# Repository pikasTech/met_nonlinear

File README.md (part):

# 电化学非线性矫正

# 2024年6月10日

1. 做非线性的数据收集，其中包括对震级的精确标定
2. 研究可以收集数据的范围
3. 在拓展可以收集的数据的范围之前，也可以先把数据的加载和处理流程进行处理

对于1，可以使用激光的数据来做标定

# 2024年6月11日

对绘图进行了增强，支持点选数据标签

激光测量结果（前9个点）：

加入校准系数后

# 2024年6月12日

考虑如何将数据加载到模型

1. review 之前跑过的代码
2. 将之前的代码跑起来（选）
3. 研究之前代码的数据集的格式，考虑方案：1.格式转换/2.格式兼容
4. 将一个数据做导入
5. 将数据按照之前的方式做处理

找到之前的笔记：

> 2023年7月5日 李昂
>
> 完成了用于训练的原始时域数据的收集，并可以进行绘图：
>
> 
>
> 用LSTM模型对系统进行辨识：
>
> 
>
> 经过训练后，最好的结果是loss=16000左右：
>
> 查看预测结果：在这个片段中预测结果和实际结果的相位基本一致，但幅值差异还是很大
>
> 
>
> 在这个片段中预测结果和实际结果的相位和幅值差异都较大
>
> 
>
> 按照结果进行初步分析，认为至少直流偏置是得到了正常的辨识的，但模型整体处于欠拟合状态，不能很好地拟合目标结果
>
> 下一步计划：
>
> 1. **数据预处理和特征工程**：
>    - 对原始时域数据进行进一步的预处理，例如去除噪声、归一化等，以提高数据质量和模型训练效果。
>    - 考虑是否需要进行特征工程，例如提取频域特征或其他相关特征，以增加模型的输入维度和表达能力。
> 2. **模型调优**：
>    - 调整模型的超参数，例如LSTM层的神经元数量、层数，调整优化器的学习率和其他参数，以提高模型的拟合能力和性能。
>    - 尝试其他类型的模型或改进的神经网络结构，例如带有注意力机制的模型或Transformer模型，以便更好地捕捉信号的时序特征。
> 3. **增加训练数据**：
>    - 如果可能，收集更多的训练数据，以增加模型的训练样本数量，从而提高模型的泛化能力和鲁棒性。
>    - 确保收集到的数据具有一定的多样性和覆盖范围，以更好地涵盖系统的不同情况和特性。
> 4. **尝试其他损失函数**：
>    - 考虑使用与频率域相关的损失函数，以更好地兼顾高频信息，例如频谱损失函数或基于相干性的损失函数。
>    - 根据任务的特点和需求，探索其他合适的损失函数或自定义损失函数，以提高模型的训练效果和适应性。
> 5. **模型集成和集成学习**：
>    - 考虑使用模型集成的方法，例如将多个训练得到的模型进行集成或进行模型融合，以获得更好的预测性能和鲁棒性。
>    - 探索集成学习的技术，例如投票、堆叠等，以提高模型的泛化能力和抗噪性。
> 6. **模型评估和性能分析**：
>    - 对模型的训练和预测结果进行全面的评估和分析，包括对预测结果的幅值、相位等进行进一步的统计和比较。
>    - 使用其他指标来评估模型的性能，例如均方根误差（RMSE）、平均绝对误差（MAE）等，以全面了解模型的预测能力和偏差。
>
> 2023年7月6日 李昂
>
> 考虑将进行多种时间尺度的采样（1Khz采样率、100Hz采样率等）同时纳入特征的方式来补充特征中的低频信息。
>
> 
>
> 三个时间尺度的采样拼合成特征，最后得到一个（48，1）形状的特征
>
> 
>
> 但是训练失败了，loss变成了nan
>
> 改变特征形状
>
> 特征形状改为(8,4)的训练效果：
>
> 
>
> 拟合效果：
>
> 
>
> 
>
> 
>
> 可以看到在高频和低频的拟合效果在一些部分都已经很好，但是当实际值频率高且有较大的偏置时预测曲线不能很好地反映偏置。

切到23年7月8日的commit，发现缺少data.csv

搜索到了同名的csv，尝试加载

可以运行，但是运行到 `model.fit` 出现了 cuda 的报错导致 python 崩溃

```
failed call to cuInit: UNKNOWN ERROR (34)
```

有可能是显卡驱动的问题，为了避免兼容问题，先考虑使用 CPU 进行训练

在 docker 里面仍然崩溃，有可能是内存限制的问题

检查了 wsl 的内存限制，32 G 已经很大，不太可能是内存问题

```
[wsl2]
memory=32GB
```

下面考虑重新用 conda  在 win 上配一个环境

参考文章

https://pieriantraining.com/tensorflow-lstm-example-a-beginners-guide/

用 conda 的 .yml 安装几乎完全是失败的，还是要用 reuirements.txt，conda 的 .yml 即使最基础的包都会冲突

可以在 win 下直接运行了

# 2024年6月17日

conda 创建新环境

```
conda create -n metnl python=3.11.9
conda activate metnl

```

# 2024年6月19日

创建了进行训练的UI

支持更多的超参数

# 2024年6月20日

训练一轮后的效果

训练两轮：

训练4轮，loss:308.22

初步跑通了对时域数据的预测，预测时间需要10分钟，需要考虑将数据输出保存

对扫频数据的响应还存在失真度高的问题：

处理 `_data.json` 的数据加载问题

LSTM模型的频率响应数据可以被导出，然后由频率响应分析程序打开

# 2024年9月23日 调研笔记

频率响应非线性是指一个系统对不同频率信号的响应不是线性的，即系统对频率的响应不能简单地通过线性方程或比例关系来描述。在许多物理、电子和声学系统中，频率响应的非线性是常见现象。

具体来说，一个系统的频率响应描述了该系统对不同频率的输入信号如何影响输出信号的幅度和相位。在理想的线性系统中，所有频率的输入信号都会按照相同的比例和相位关系被传输，这意味着输出信号的频率成分与输入信号完全一致，只是幅度和相位可能发生变化。

然而，对于非线性系统，频率响应可能随频率的变化而变化，不同频率的信号可能引起系统的不同响应。这种响应可能包括：

1. **谐波失真**：输入信号在系统中产生频率是原始频率整数倍的谐波。
2. **互调失真**：多个频率的输入信号相互作用，在输出中产生非原始频率的额外频率（例如两个输入频率的和或差）。
3. **幅度饱和**：当输入信号的幅度超过某个阈值时，输出信号的幅度不再与输入成比例增加。
4. **相位非线性**：系统对不同频率信号的相位延迟不是线性的，可能导致信号波形的畸变。

这种非线性行为在设计和评估音响设备、无线通信系统、传感器等方面非常重要，因为它们会影响系统的性能和信号的质量。在实际应用中，通常需要通过各种方法来衡量和补偿这些非线性特性，以提高系统的整体性能。

### 非线性系统特性

在非线性系统中，系统参数（如弹性系数、阻尼系数）可能不是常数，而是依赖于状态变量（如位移、速度）或输入的幅度。这种依赖性意味着系统的响应与输入不成简单的线性关系。以下是一些典型的非线性系统特性：

1. **非恒定弹性系数的弹簧**：
   - 弹簧的刚度可能随着弹簧的伸长或压缩程度而改变。例如，在某些材料中，刚度在经过某个变形阈值后可能增加或减少，这会影响系统的动态响应特性。
2. **非线性阻尼**：
   - 阻尼系数可能不是恒定的，而是依赖于速度或位移的幅度。例如，在粘性阻尼中，阻尼力可能与速度的幂次方成正比，这与常见的线性阻尼（阻尼力与速度成正比）不同。
3. **几何非线性**：
   - 在结构力学中，由于结构形变较大，原有的线性位移-应力关系不再适用，必须使用更复杂的模型来描述结构的实际行为。

### 对系统行为的影响

非线性特性可以导致系统行为表现出一些独特的特点：

- **频率变化**：系统的自然频率可能随着振幅的增加而变化，导致所谓的幅度依赖频率现象。
- **非线性共振**：系统在特定的驱动频率下可能表现出异常的响应。
- **双稳态或多稳态行为**：在某些条件下，系统可能存在两个或多个稳定平衡状态，使得系统的动态响应依输入历史而变化。
- **混沌现象**：在特定的参数和初始条件下，系统的响应可能是不可预测的，即便是微小的输入变化也能导致显著不同的输出行为。

### 应对策略

理解和处理这些非线性特性需要使用高级的数学模型和仿真技术。在实际工程实践中，可能需要采用非线性系统理论、数值方法和实验研究来准确预测和调控这些复杂的系统行为。例如，通过调整系统设计或使用非线性控制策略，可以优化系统的性能或抑制不希望的非线性效应。

使用神经网络对非线性系统进行建模和识别，进而通过逆网络实现补偿以达到线性系统的效果，是控制理论和机器学习领域的一个活跃研究方向。神经网络由于其强大的非线性拟合能力，特别适用于模拟和补偿复杂的非线性系统动态。

### 基本方法

1. **系统识别（Forward Modeling）**：使用神经网络学习系统的输入-输出关系，构建一个预测模型。这种模型可以是前馈神经网络、循环神经网络或更复杂的结构，根据系统的动态特性和数据的时间序列特性选择。
2. **逆模型设计（Inverse Modeling）**：基于系统识别得到的模型，设计一个逆网络模型，即输入希望得到的输出，网络输出实现该输出所需的输入。逆模型通常用于控制应用，通过逆模型可以生成使系统输出达到预期的控制输入。

### 经典论文和资源

以下是一些相关的经典论文和资源，它们提供了使用神经网络进行系统识别和控制的深入分析：

1. **Hunt, K.J., Sbarbaro, D., Żbikowski, R., & Gawthrop, P.J. (1992)**, "Neural networks for control systems—A survey," *Automatica*, vol. 28, no. 6, pp. 1083-1112.
   - 这篇论文是早期关于使用神经网络进行控制系统建模和控制的综述，涵盖了基础概念和多个案例研究。
2. **Lewis, F.L., Jagannathan, S., & Yesildirak, A. (1999)**, *Neural Network Control of Robot Manipulators and Nonlinear Systems*. Taylor & Francis.
   - 这本书详细讨论了神经网络在机器人操纵器和非线性系统控制中的应用，包括前馈和反馈控制策略。
3. **Narendra, K.S. & Parthasarathy, K. (1990)**, "Identification and control of dynamical systems using neural networks," *IEEE Transactions on Neural Networks*, vol. 1, no. 1, pp. 4-27.
   - 这篇文章是神经网络用于动态系统识别和控制的经典研究，特别是在逆控制框架中的应用。
4. **Werbos, P.J. (1990)**, "Backpropagation through time: what it does and how to do it," *Proceedings of the IEEE*, vol. 78, no. 10, pp. 1550-1560.
   - 这篇文章介绍了通过时间反向传播算法（BPTT），适用于循环神经网络，这种网络结构非常适合处理系统动态识别和预测。

### 实践考虑

- 确保有足够的数据来训练网络，特别是在复杂的非线性系统中。
- 考虑使用最新的神经网络架构和训练技术，如深度学习、强化学习等。
- 注意模型的泛化能力和逆模型的稳定性，特别是在控制应用中。

如果你需要更具体的资源或对某个方面有特别的兴趣，我可以帮助你查找更多相关文献或提供进一步的指导。

## 关键论文1 Domain Adaptation Extreme Learning Machines for Drift Compensation in E-Nose Systems

这篇论文《Domain Adaptation Extreme Learning Machines for Drift Compensation in E-Nose Systems》由Lei Zhang 和 David Zhang 撰写，主要研究了电子鼻（E-nose）系统中的传感器漂移问题。传感器漂移是指传感器在长时间运行后，由于老化或环境变化等因素，其检测性能会发生非线性动态变化，影响气体识别的准确性和稳定性。

### 系统特征：

- **非线性动态属性**：传感器漂移表现为非线性动态特性，使得简单的线性校正方法难以有效预测和补偿。
- **多传感器电子鼻系统**：研究涉及多个传感器，每个传感器都可能发生漂移，这增加了整个系统行为和漂移补偿的复杂性。

### 使用的方法：

- **领域适应极限学习机（DAELM）**：该框架将极限学习机（ELM）扩展到能够处理领域适应问题，帮助提高ELM在不同领域（不同时间或条件下的传感器读数）间的迁移能力。

- 两种算法—DAELM-S和DAELM-T

  ：

  - **DAELM-S（源DAELM）**：使用源域（初始传感器读数）的标记数据和目标域（漂移发生后的读数）的有限标记样本来学习分类器。
  - **DAELM-T（目标DAELM）**：主要利用目标域的有限标记样本学习，同时利用大量未标记数据通过逼近预学习基分类器的预测来学习。

### 与之前讨论的相关性：

该方法直接关联到之前讨论的使用神经网络进行系统识别和逆模型补偿非线性系统行为的概念。通过采用领域适应策略，DAELM框架有效地应对了由于漂移导致的传感器行为随时间变化的问题，使用先进的机器学习技术动态地适应新条件，无需广泛的重新训练或重新校准。这种方法与使用神经网络处理动态和非线性系统的概念非常吻合，为实时应用中维持系统准确性提供了一种复杂的方法。
## 关键论文2 Mitigation of SOA-Induced Nonlinearity With the Aid of Deep Learning Neural Networks
在分析的论文《Mitigation of SOA-Induced Nonlinearity With the Aid of Deep Learning Neural Networks》中，研究团队探讨了使用深度学习神经网络来补偿由半导体光放大器（SOA）引起的非线性。

系统频率响应的非线性特征
在这篇论文中，SOA的非线性主要表现为增益饱和现象。随着输入光功率的增加，SOA的增益开始饱和，导致其输出特性与输入特性之间的非线性关系增强。这种增益饱和确实导致系统的频率响应随着幅度变化而呈现非线性特征。

构建数据集
作者通过模拟实验生成数据集，使用了100 Gbit/s的PAM4信号，通过80公里的标准单模光纤传输，并通过18 GHz的电吸收调制激光器（EML）进行光学调制。此外，还采用了两个串联的SOA，模拟不同的非线性条件，以评估各种神经网络模型对非线性补偿的效果。

输入数据
输入数据包括由EML生成的经SOA处理后的PAM4信号，这些信号在传输和放大过程中经历了非线性变形，主要用于训练和测试深度学习模型。

评价补偿效果
补偿效果通过比特误码率（BER）来评估，使用了深度神经网络（DNN）、卷积神经网络（CNN）和长短期记忆网络（LSTM）三种模型进行补偿。实验结果显示，LSTM在处理SOA引起的非线性补偿中表现最佳，能显著提高接收灵敏度，相较于DNN和CNN有更好的等化性能。

与非线性频率响应补偿的关联性
这篇论文的研究与我们之前讨论的使用神经网络对非线性系统进行识别和逆建模补偿非线性频率响应非常相关。通过机器学习技术，尤其是LSTM，可以有效地识别和补偿因SOA增益饱和引起的非线性，这种方法在处理任何形式的系统非线性特征时都显示出了潜力。

LSTM 有更好的非线性表达能力

## 关键论文3 Long Short-Term Memory (LSTM) Neural Network-based System Identification and Augmented Predictive Control of Piezoelectric Actuators

电化学和 PZT 有类似的非线性特点，可以被当作类似的主题

# 2024年6月27日 GPU 加速

看了一下 nvidia-smi，目前的CUDA版本是12.2

下载的CUDA版本是12.5，升级一下GPU驱动试试

更新后可以使用12.5的CUDA了

但是 tensorflow 还是不能识别

```python
>>> tf.test.is_gpu_available()   
>>> WARNING:tensorflow:From <stdin>:1: is_gpu_available (from tensorflow.python.framework.test_util) is deprecated and will be removed in a future version.
>>> Instructions for updating:
>>> Use `tf.config.list_physical_devices('GPU')` instead.
>>> 2024-06-27 16:54:11.702807: I tensorflow/core/platform/cpu_feature_guard.cc:210] This TensorFlow binary is optimized to use available CPU instructions in performance-critical operations.
>>> To enable the following instructions: AVX2 FMA, in other operations, rebuild TensorFlow with the appropriate compiler flags.
>>> False
>>> tf.config.list_physical_devices('GPU')
>>> []
>>> 
```

重启之后还是只能识别到 CPU

``` python
>>> tf.config.list_physical_devices()
[PhysicalDevice(name='/physical_device:CPU:0', device_type='CPU')]
```

检查 tensorflow 文档，发现对 CUDA 和 cuDNN 的版本有明确要求

需要重新安装 CUDA 11.2 和 cuDNN 8.1.0

重新安装还是不行，可能是tensorflow版本问题

在CMD中可以正确识别GPU，需要py3.9+tf2.6

用原来的py3.11+tf2.15不能识别GPU

# 2024年6月28日 GPU 内存不足问题

```
2024-06-28 10:11:44.894887: W tensorflow/core/common_runtime/bfc_allocator.cc:457] Allocator (GPU_0_bfc) ran out of memory trying to allocate 4.90GiB (rounded to 5262653440)requested by op _EagerConst
```

减少了 `units` 的值，`batch_size` 的值和 `epochs` 的值

```
2024-06-28 10:21:02.480902: W tensorflow/core/common_runtime/bfc_allocator.cc:457] Allocator (GPU_0_bfc) ran out of memory trying to allocate 4.90GiB (rounded to 5262653440)requested by op _EagerConst
```

还是需要 4.9 GB

继续调整参数，显存调到了2.3G

训练数据的点数（通过 `train_split` 截取）会影响训练量和内存

#### 特征缓存没有正确更新的问题

    data_length = len(input_data)
    filename = "cache/cache_" + \
        "_".join(map(str, [n_timesteps] + freq_list + [data_length])) + ".npz"

缓存文件的命名要包含所有影响缓存结果的参数，这样参数变化后才会重新生成缓存

启用GPU的训练时间

CPU 训练时间

对比测试发现使用 GPU 反而还更慢了

batch size 增到到128

这时候训练速度和 CPU 接近

batch size 调到 10000 也不会超显存，而且速度很快，这说明使用 GPU 时应该尽可能地增加 batch size

在切换 CPU 和 GPU 的时候，会提示不能在初始化之后切换，目前只能重启应用，然后在开始其他操作之前先切换好 CPU/GPU

在 batch_size 足够大的时候才能更体现出 GPU 的优势

在  batch_size 足够大的情况下，训练时间由2:22/Epoch 缩短到了0:11/Epoch

unit = 128 的情况下loss 很快收敛到 71 附近，拟合效果不是很好

units = 16 的结果类似

units 代表了 LSTM 的模型的复杂度，复杂度低时对训练数据的拟合能力较弱，但是扫频输出会更接近正弦

units 较高时对训练数据的拟合能力更强，但是扫频输出会更非线性

### 分批加载数据

```python
class DataGenerator(Sequence):
    def __init__(self, X_data, Y_data, batch_size=128):
        print("Creating data generator...")
        print("Batch size:", batch_size)
        print("Data shape:", X_data.shape, Y_data.shape)
        self.X_data = X_data
        self.Y_data = Y_data
        self.batch_size = batch_size
        self.indices = np.arange(len(X_data))

    def __len__(self):
        return int(np.ceil(len(self.X_data) / self.batch_size))

    def __getitem__(self, index):
        batch_indices = self.indices[index *
                                     self.batch_size:(index + 1) * self.batch_size]
        X_batch = self.X_data[batch_indices]
        Y_batch = self.Y_data[batch_indices]
        return X_batch, Y_batch

    def on_epoch_end(self):
        np.random.shuffle(self.indices)

def train_module(model, train_X, train_Y, model_weights_path='model/model.weights.h5', batch_size=128, epochs=1):
    print("Training model...")
    print("Model weights path:", model_weights_path)
    print("Batch size:", batch_size)
    print("Epochs:", epochs)
    print("Train data shape:", train_X.shape, train_Y.shape)
    train_generator = DataGenerator(train_X, train_Y, batch_size=batch_size)

    checkpoint = ModelCheckpoint(model_weights_path, save_weights_only=True)
    checkpoint2 = ModelCheckpoint(
        f'model/model{{epoch:02d}}.weights.h5', save_weights_only=True)

    model.fit(train_generator, epochs=epochs, verbose=1,
              callbacks=[checkpoint, checkpoint2])
```

引入了一个数据迭代器，分批加载待训练数据，可以大幅降低显存占用，支持训练更长的数据

### 较好的结果1 :units=16

### units = 8

#### loss = 356

局部放大

#### 训练中断

```
18/37 [=============>................] - ETA: 4s - loss: 352.3407Error executing callback: Could not synchronize CUDA stream: CUDA_ERROR_ILLEGAL_ADDRESS: an illegal memory access was encountered
Traceback (most recent call last):
  File "D:\Work\met_nonlinear\calibration_analyzer\adjuster.py", line 414, in on_click
    self.callback()
  File "D:\Work\met_nonlinear\calibration_analyzer\adjuster.py", line 609, in on_widget_change
    self.callback(updated_values)
  File "D:\Work\met_nonlinear\ui.py", line 48, in panel_update
    metnl.train_module(model, train_X, train_Y,
  File "D:\Work\met_nonlinear\metnl.py", line 323, in train_module
    model.fit(train_generator, epochs=epochs, verbose=1,
  File "C:\Users\lyon\MiniConda3\envs\tf26\lib\site-packages\keras\engine\training.py", line 1189, in fit
    callbacks.on_train_batch_end(end_step, logs)
  File "C:\Users\lyon\MiniConda3\envs\tf26\lib\site-packages\keras\callbacks.py", line 435, in on_train_batch_end
    self._call_batch_hook(ModeKeys.TRAIN, 'end', batch, logs=logs)
  File "C:\Users\lyon\MiniConda3\envs\tf26\lib\site-packages\keras\callbacks.py", line 295, in _call_batch_hook
    self._call_batch_end_hook(mode, batch, logs)
  File "C:\Users\lyon\MiniConda3\envs\tf26\lib\site-packages\keras\callbacks.py", line 315, in _call_batch_end_hook
    self._call_batch_hook_helper(hook_name, batch, logs)
  File "C:\Users\lyon\MiniConda3\envs\tf26\lib\site-packages\keras\callbacks.py", line 353, in _call_batch_hook_helper
    hook(batch, logs)
  File "C:\Users\lyon\MiniConda3\envs\tf26\lib\site-packages\keras\callbacks.py", line 1028, in on_train_batch_end
    self._batch_update_progbar(batch, logs)
  File "C:\Users\lyon\MiniConda3\envs\tf26\lib\site-packages\keras\callbacks.py", line 1100, in _batch_update_progbar
    logs = tf_utils.sync_to_numpy_or_python_type(logs)
  File "C:\Users\lyon\MiniConda3\envs\tf26\lib\site-packages\keras\utils\tf_utils.py", line 516, in sync_to_numpy_or_python_type
    return tf.nest.map_structure(_to_single_numpy_or_python_type, tensors)
  File "C:\Users\lyon\MiniConda3\envs\tf26\lib\site-packages\tensorflow\python\util\nest.py", line 869, in map_structure
    structure[0], [func(*x) for x in entries],
  File "C:\Users\lyon\MiniConda3\envs\tf26\lib\site-packages\tensorflow\python\util\nest.py", line 869, in <listcomp>
    structure[0], [func(*x) for x in entries],
  File "C:\Users\lyon\MiniConda3\envs\tf26\lib\site-packages\keras\utils\tf_utils.py", line 512, in _to_single_numpy_or_python_type
    x = t.numpy()
  File "C:\Users\lyon\MiniConda3\envs\tf26\lib\site-packages\tensorflow\python\framework\ops.py", line 1094, in numpy
    maybe_arr = self._numpy()  # pylint: disable=protected-access
  File "C:\Users\lyon\MiniConda3\envs\tf26\lib\site-packages\tensorflow\python\framework\ops.py", line 1062, in _numpy
    six.raise_from(core._status_to_exception(e.code, e.message), None)  # pylint: disable=protected-access
  File "<string>", line 3, in raise_from
tensorflow.python.framework.errors_impl.InternalError: Could not synchronize CUDA stream: CUDA_ERROR_ILLEGAL_ADDRESS: an illegal memory access was encountered
```

应该是显存接近满了导致的，降低 batch_size，试了 800000 不能跑太久

显存占用 3.3 G 可以较长时间运行

#### loss = 240

放大图，高频失真度有明显改善

loss = 240 后有训练了 1000 epochs，loss 仍在 240 附近

继续训练后：

# 2024年7月2日

频率特性曲线

失真度下降到了20%左右

预测更多频点

更多点的结果

# 2024年7月17日 周报告

   为了通过优化 GPU 加速训练过程，提高深度学习模型的训练效率，并解决在 GPU 加速过程中遇到的内存不足和设备识别等问题，我们进行了这一系列实验。通过调整训练参数、升级 CUDA 版本和优化模型结构，希望能够显著缩短训练时间并提高模型的性能。

   ## GPU 加速训练问题

   ### CUDA 版本

   查看 nvidia-smi，当前 CUDA 版本为 12.2

   下载 CUDA 版本为 12.5，准备升级 GPU 驱动

   更新后，可以使用 CUDA 12.5

   但 TensorFlow 仍无法识别 GPU

   重启后仍然只能识别 CPU

   检查 TensorFlow 文档发现需要特定版本的 CUDA 和 cuDNN

   重新安装 CUDA 11.2 和 cuDNN 8.1.0 仍无效，怀疑是 TensorFlow 版本问题

   在 CMD 中可以正确识别 GPU，需使用 Python 3.9 和 TensorFlow 2.6

   使用 Python 3.11 和 TensorFlow 2.15 无法识别 GPU

   ### 小结

   尝试不同版本的 CUDA 和 cuDNN 以使 TensorFlow 识别 GPU 是解决 GPU 加速训练问题的关键。建议严格遵循 TensorFlow 官方文档提供的兼容版本来配置环境。

   ## GPU 内存不足问题

   ### 调整参数

   减少 `units`、`batch_size` 和 `epochs` 的值后仍需 4.9 GB 内存

   调整参数后显存占用调至 2.3 GB

   训练数据的点数影响训练量和内存

   ### 特征缓存未正确更新的问题

   缓存文件的命名需包含所有影响缓存结果的参数，以确保参数变化后重新生成缓存

   ### 训练时间比较

   启用 GPU 的训练时间

   CPU 训练时间

   对比测试发现使用 GPU 反而更慢

   将 batch size 增加到 128

   此时训练速度与 CPU 接近

   batch size 增加到 10000 不会超显存，速度也很快，说明使用 GPU 时应尽可能增加 batch size

   切换 CPU 和 GPU 时需重启应用，并在其他操作前先切换好 CPU/GPU

   在 batch_size 足够大时，GPU 优势明显

   训练时间从 2:22/Epoch 缩短至 0:11/Epoch

   unit = 128 的情况下 loss 很快收敛到 71 附近，拟合效果一般

   units = 16 的结果类似

   ### LSTM 模型复杂度

   units 表示 LSTM 模型的复杂度，复杂度低时对训练数据的拟合能力较弱，但扫频输出接近正弦

   units 高时对训练数据的拟合能力强，但扫频输出更非线性

   ### 分批加载数据

   引入数据迭代器，分批加载待训练数据，可大幅降低显存占用，支持训练更长的数据

说明通过调整 batch size 和引入数据迭代器，可以显著优化 GPU 的显存使用效率，使得模型在 GPU 上的训练速度和效果得到提升。

   ## 较好的结果

   ### units = 8

   #### loss = 356

   #### 训练中断

   显存接近满导致，降低 batch_size 至 800000 仍无法长时间运行

   显存占用 3.3 GB 可较长时间运行

   #### loss = 240

   放大图，高频失真度改善

   loss = 240 后训练 1000 epochs，loss 仍在 240 附近

   继续训练后：

   ## 频率特性曲线

   失真度降至 20%

   ### 预测更多频点

   ### 更多点的结果

 说明通过优化模型参数和批量处理技术，显著改善了训练效率和结果质量，特别是在高频预测上的表现有了显著提高。

   ## 下一步计划

   1. 进一步优化模型结构，尝试其他深度学习模型以提升预测精度。
   2. 探索更多数据预处理方法，提升数据质量和模型训练效果。
   3. 扩展实验规模，增加训练数据量，验证模型的泛化能力。
   4. 开发自动化的参数调整和模型选择工具，提高实验效率。

# 2024年8月22日

预测数据中的突变都在同一个时刻，是初值问题的可能性比较大

在用LSTM训练出的模型进行预测时，最开始的一段数据表现总是和后面的数据差别很大，这是否可能是前一段的数据的特征缺失数据，因为特征总是向前面的数据采用得到的，而最开始的一段数据没有前面的历史数据。LSTM（长短期记忆网络）模型在进行预测时，确实可能会在序列的开头部分表现出与后续部分不同的预测结果，这主要有以下几个原因：

1. **初始状态不充分**：LSTM模型依赖于前面的数据来建立其内部状态（即记忆）。在序列的开头，模型还没有看到足够多的数据来完全捕捉序列的模式，导致模型的初始预测可能不准确。随着输入序列逐渐增加，LSTM能够更好地学习和捕捉数据中的时间依赖性，因此后续的数据预测会更准确。
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
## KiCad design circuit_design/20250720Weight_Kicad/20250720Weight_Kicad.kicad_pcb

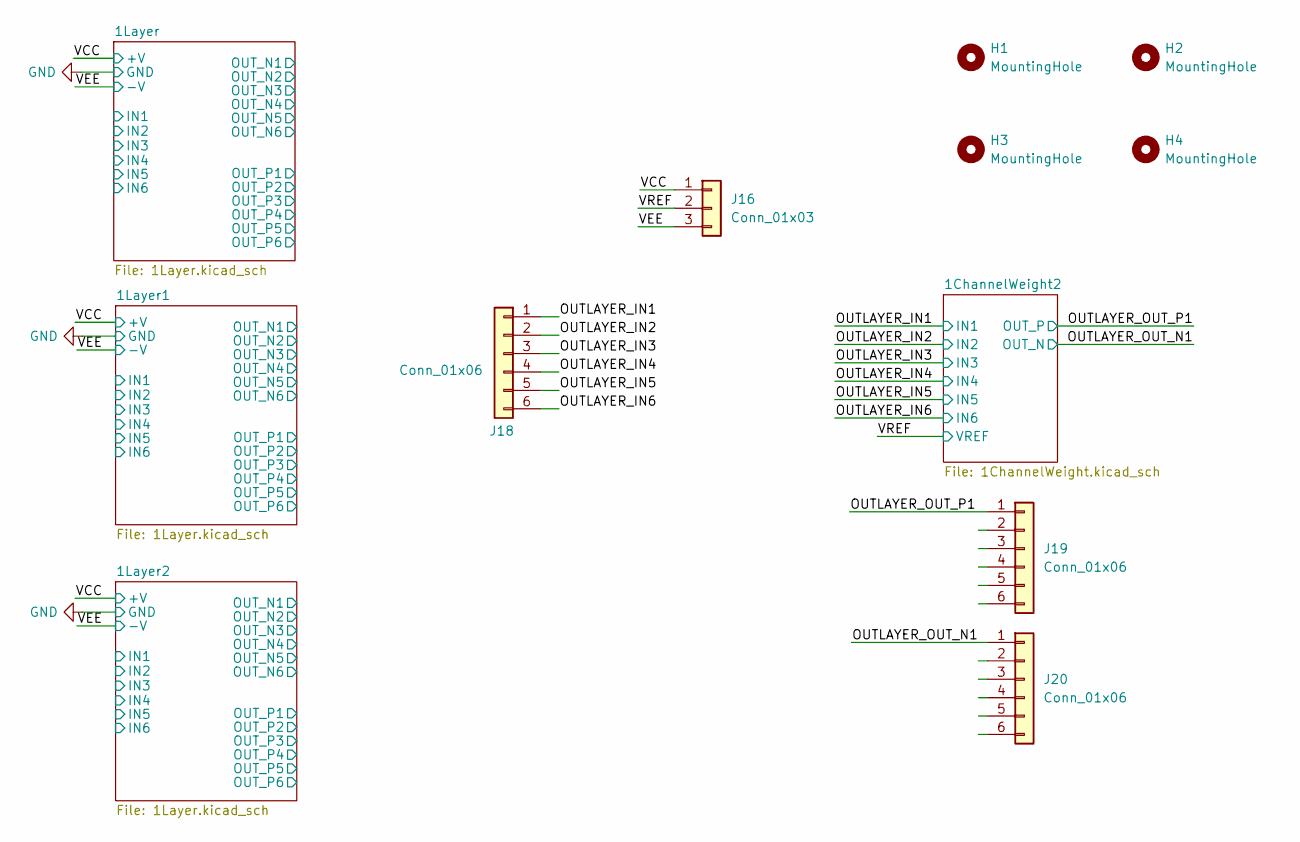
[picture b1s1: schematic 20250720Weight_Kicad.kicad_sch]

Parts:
H1, H2, H3, H4: MountingHole; MountingHole_3.2mm_M3
J16: Conn_01x03; PinHeader_1x03_P2.54mm_Vertical
J18, J19, J20: Conn_01x06; PinSocket_1x06_P2.54mm_Vertical

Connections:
/OUTLAYER_IN1: J18.1; also elsewhere on the board
/OUTLAYER_IN2: J18.2; also elsewhere on the board
/OUTLAYER_IN3: J18.3; also elsewhere on the board
/OUTLAYER_IN4: J18.4; also elsewhere on the board
/OUTLAYER_IN5: J18.5; also elsewhere on the board
/OUTLAYER_IN6: J18.6; also elsewhere on the board
/OUTLAYER_OUT_N1: J20.1; also elsewhere on the board
/OUTLAYER_OUT_P1: J19.1; also elsewhere on the board
/VCC: J16.1; also elsewhere on the board
/VEE: J16.3; also elsewhere on the board
/VREF: J16.2; also elsewhere on the board

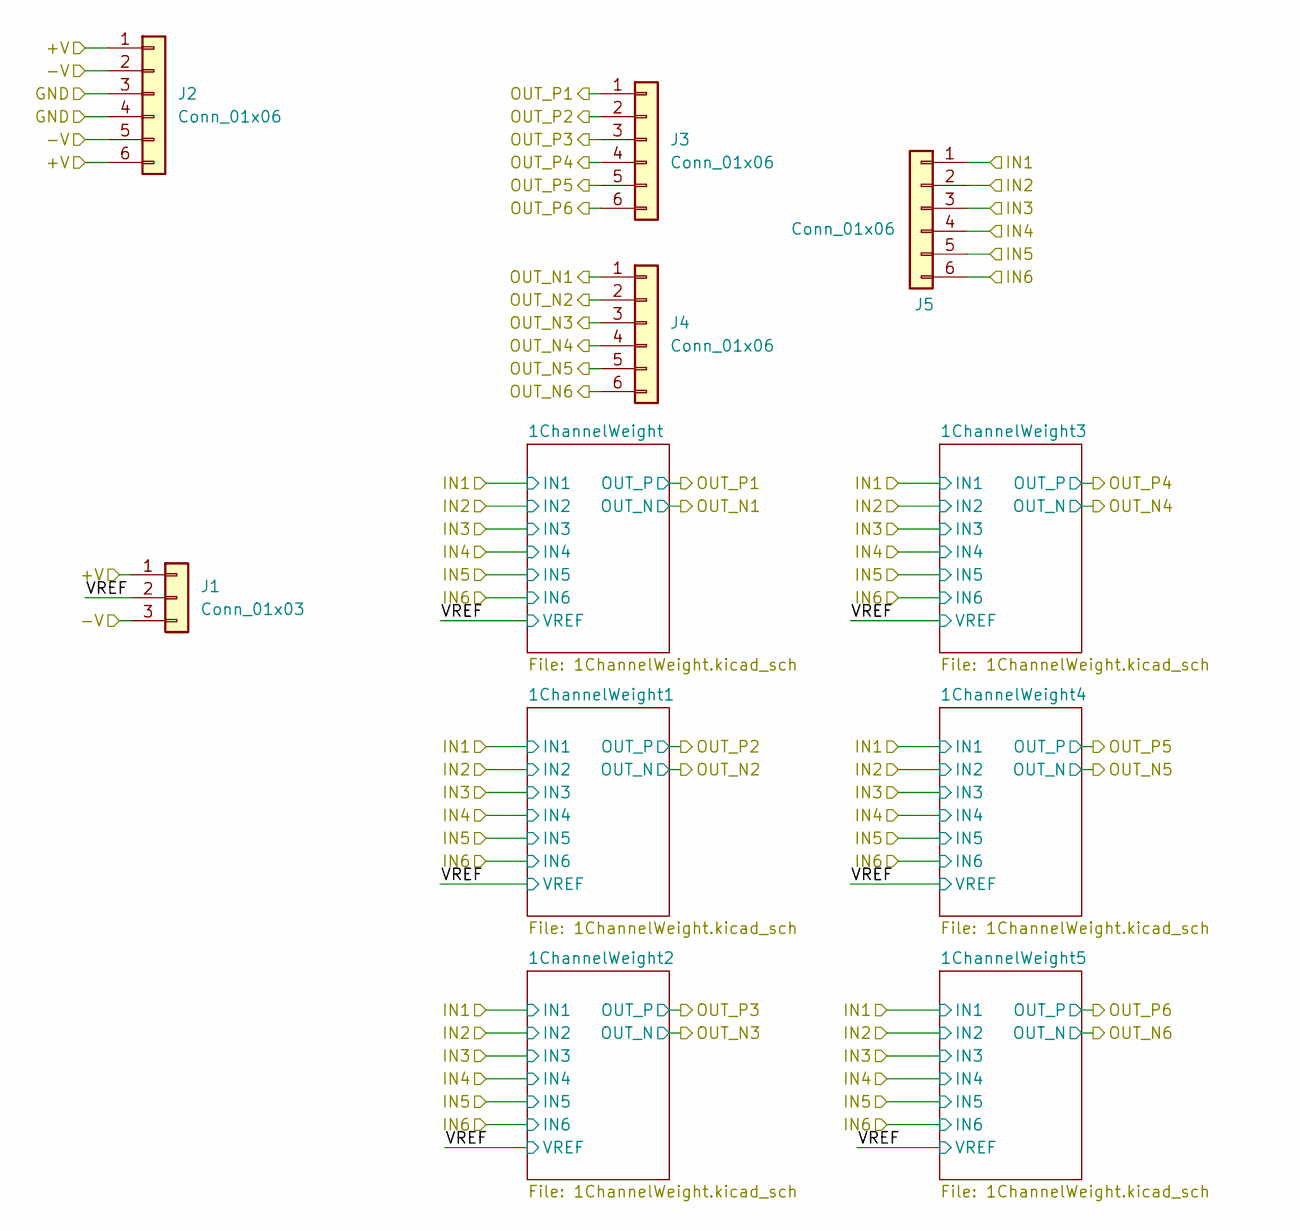
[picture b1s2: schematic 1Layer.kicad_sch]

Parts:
J1: Conn_01x03; PinHeader_1x03_P2.54mm_Vertical
J2, J3, J4, J5: Conn_01x06; PinSocket_1x06_P2.54mm_Vertical

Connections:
/1Layer/IN1: J5.1; also elsewhere on the board
/1Layer/IN2: J5.2; also elsewhere on the board
/1Layer/IN3: J5.3; also elsewhere on the board
/1Layer/IN4: J5.4; also elsewhere on the board
/1Layer/IN5: J5.5; also elsewhere on the board
/1Layer/IN6: J5.6; also elsewhere on the board
/1Layer/OUT_N1: J4.1; also elsewhere on the board
/1Layer/OUT_N2: J4.2; also elsewhere on the board
/1Layer/OUT_N3: J4.3; also elsewhere on the board
/1Layer/OUT_N4: J4.4; also elsewhere on the board
/1Layer/OUT_N5: J4.5; also elsewhere on the board
/1Layer/OUT_N6: J4.6; also elsewhere on the board
/1Layer/OUT_P1: J3.1; also elsewhere on the board
/1Layer/OUT_P2: J3.2; also elsewhere on the board
/1Layer/OUT_P3: J3.3; also elsewhere on the board
/1Layer/OUT_P4: J3.4; also elsewhere on the board
/1Layer/OUT_P5: J3.5; also elsewhere on the board
/1Layer/OUT_P6: J3.6; also elsewhere on the board
/1Layer/VREF: J1.2; also elsewhere on the board
/VCC: J1.1, J2.1, J2.6; also elsewhere on the board
/VEE: J1.3, J2.2, J2.5; also elsewhere on the board
GND: J2.3, J2.4; also elsewhere on the board

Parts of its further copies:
J6, J8, J9, J10, J11, J13, J14, J15: Conn_01x06; PinSocket_1x06_P2.54mm_Vertical
J7, J12: Conn_01x03; PinHeader_1x03_P2.54mm_Vertical

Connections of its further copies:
/1Layer1/IN1: J10.1; also elsewhere on the board
/1Layer1/IN2: J10.2; also elsewhere on the board
/1Layer1/IN3: J10.3; also elsewhere on the board
/1Layer1/IN4: J10.4; also elsewhere on the board
/1Layer1/IN5: J10.5; also elsewhere on the board
/1Layer1/IN6: J10.6; also elsewhere on the board
/1Layer1/OUT_N1: J9.1; also elsewhere on the board
/1Layer1/OUT_N2: J9.2; also elsewhere on the board
/1Layer1/OUT_N3: J9.3; also elsewhere on the board
/1Layer1/OUT_N4: J9.4; also elsewhere on the board
/1Layer1/OUT_N5: J9.5; also elsewhere on the board
/1Layer1/OUT_N6: J9.6; also elsewhere on the board
/1Layer1/OUT_P1: J8.1; also elsewhere on the board
/1Layer1/OUT_P2: J8.2; also elsewhere on the board
/1Layer1/OUT_P3: J8.3; also elsewhere on the board
/1Layer1/OUT_P4: J8.4; also elsewhere on the board
/1Layer1/OUT_P5: J8.5; also elsewhere on the board
/1Layer1/OUT_P6: J8.6; also elsewhere on the board
/1Layer1/VREF: J7.2; also elsewhere on the board
/1Layer2/IN1: J15.1; also elsewhere on the board
/1Layer2/IN2: J15.2; also elsewhere on the board
/1Layer2/IN3: J15.3; also elsewhere on the board
/1Layer2/IN4: J15.4; also elsewhere on the board
/1Layer2/IN5: J15.5; also elsewhere on the board
/1Layer2/IN6: J15.6; also elsewhere on the board
/1Layer2/OUT_N1: J14.1; also elsewhere on the board
/1Layer2/OUT_N2: J14.2; also elsewhere on the board
/1Layer2/OUT_N3: J14.3; also elsewhere on the board
/1Layer2/OUT_N4: J14.4; also elsewhere on the board
/1Layer2/OUT_N5: J14.5; also elsewhere on the board
/1Layer2/OUT_N6: J14.6; also elsewhere on the board
/1Layer2/OUT_P1: J13.1; also elsewhere on the board
/1Layer2/OUT_P2: J13.2; also elsewhere on the board
/1Layer2/OUT_P3: J13.3; also elsewhere on the board
/1Layer2/OUT_P4: J13.4; also elsewhere on the board
/1Layer2/OUT_P5: J13.5; also elsewhere on the board
/1Layer2/OUT_P6: J13.6; also elsewhere on the board
/1Layer2/VREF: J12.2; also elsewhere on the board
/VCC: J6.1, J6.6, J7.1, J11.1, J11.6, J12.1; also elsewhere on the board
/VEE: J6.2, J6.5, J7.3, J11.2, J11.5, J12.3; also elsewhere on the board
GND: J6.3, J6.4, J11.3, J11.4; also elsewhere on the board

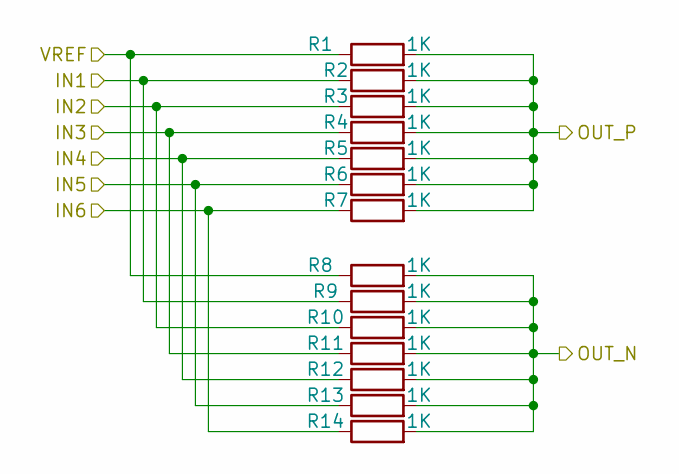
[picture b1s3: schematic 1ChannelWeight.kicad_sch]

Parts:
R1, R2, R3, R4, R5, R6, R7, R8, R9, R10, R11, R12, R13, R14: 1K; R_0805_2012Metric

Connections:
/1Layer/IN1: R2.1, R9.1; also elsewhere on the board
/1Layer/IN2: R3.1, R10.1; also elsewhere on the board
/1Layer/IN3: R4.1, R11.1; also elsewhere on the board
/1Layer/IN4: R5.1, R12.1; also elsewhere on the board
/1Layer/IN5: R6.1, R13.1; also elsewhere on the board
/1Layer/IN6: R7.1, R14.1; also elsewhere on the board
/1Layer/OUT_N1: R8.2, R9.2, R10.2, R11.2, R12.2, R13.2, R14.2; also elsewhere on the board
/1Layer/OUT_P1: R1.2, R2.2, R3.2, R4.2, R5.2, R6.2, R7.2; also elsewhere on the board
/1Layer/VREF: R1.1, R8.1; also elsewhere on the board

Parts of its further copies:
R15, R16, R17, R18, R19, R20, R21, R22, R23, R24, R25, R26, R27, R28, R29, R30, R31, R32, R33, R34, R35, R36, R37, R38, R39, R40, R41, R42, R43, R44, R45, R46, R47, R48, R49, R50, R51, R52, R53, R54, R55, R56, R57, R58, R59, R60, R61, R62, R63, R64, R65, R66, R67, R68, R69, R70, R71, R72, R73, R74, R75, R76, R77, R78, R79, R80, R81, R82, R83, R84, R85, R86, R87, R88, R89, R90, R91, R92, R93, R94, R95, R96, R97, R98, R99, R100, R101, R102, R103, R104, R105, R106, R107, R108, R109, R110, R111, R112, R113, R114, R115, R116, R117, R118, R119, R120, R121, R122, R123, R124, R125, R126, R127, R128, R129, R130, R131, R132, R133, R134, R135, R136, R137, R138, R139, R140, R141, R142, R143, R144, R145, R146, R147, R148, R149, R150, R151, R152, R153, R154, R155, R156, R157, R158, R159, R160, R161, R162, R163, R164, R165, R166, R167, R168, R169, R170, R171, R172, R173, R174, R175, R176, R177, R178, R179, R180, R181, R182, R183, R184, R185, R186, R187, R188, R189, R190, R191, R192, R193, R194, R195, R196, R197, R198, R199, R200, R201, R202, R203, R204, R205, R206, R207, R208, R209, R210, R211, R212, R213, R214, R215, R216, R217, R218, R219, R220, R221, R222, R223, R224, R225, R226, R227, R228, R229, R230, R231, R232, R233, R234, R235, R236, R237, R238, R239, R240, R241, R242, R243, R244, R245, R246, R247, R248, R249, R250, R251, R252, R253, R254, R255, R256, R257, R258, R259, R260, R261, R262, R263, R264, R265, R266: 1K; R_0805_2012Metric

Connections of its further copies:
/1Layer1/IN1: R86.1, R93.1, R100.1, R107.1, R114.1, R121.1, R128.1, R135.1, R142.1, R149.1, R156.1, R163.1; also elsewhere on the board
/1Layer1/IN2: R87.1, R94.1, R101.1, R108.1, R115.1, R122.1, R129.1, R136.1, R143.1, R150.1, R157.1, R164.1; also elsewhere on the board
/1Layer1/IN3: R88.1, R95.1, R102.1, R109.1, R116.1, R123.1, R130.1, R137.1, R144.1, R151.1, R158.1, R165.1; also elsewhere on the board
/1Layer1/IN4: R89.1, R96.1, R103.1, R110.1, R117.1, R124.1, R131.1, R138.1, R145.1, R152.1, R159.1, R166.1; also elsewhere on the board
/1Layer1/IN5: R90.1, R97.1, R104.1, R111.1, R118.1, R125.1, R132.1, R139.1, R146.1, R153.1, R160.1, R167.1; also elsewhere on the board
/1Layer1/IN6: R91.1, R98.1, R105.1, R112.1, R119.1, R126.1, R133.1, R140.1, R147.1, R154.1, R161.1, R168.1; also elsewhere on the board
/1Layer1/OUT_N1: R92.2, R93.2, R94.2, R95.2, R96.2, R97.2, R98.2; also elsewhere on the board
/1Layer1/OUT_N2: R106.2, R107.2, R108.2, R109.2, R110.2, R111.2, R112.2; also elsewhere on the board
/1Layer1/OUT_N3: R120.2, R121.2, R122.2, R123.2, R124.2, R125.2, R126.2; also elsewhere on the board
/1Layer1/OUT_N4: R134.2, R135.2, R136.2, R137.2, R138.2, R139.2, R140.2; also elsewhere on the board
/1Layer1/OUT_N5: R148.2, R149.2, R150.2, R151.2, R152.2, R153.2, R154.2; also elsewhere on the board
/1Layer1/OUT_N6: R162.2, R163.2, R164.2, R165.2, R166.2, R167.2, R168.2; also elsewhere on the board
/1Layer1/OUT_P1: R85.2, R86.2, R87.2, R88.2, R89.2, R90.2, R91.2; also elsewhere on the board
/1Layer1/OUT_P2: R99.2, R100.2, R101.2, R102.2, R103.2, R104.2, R105.2; also elsewhere on the board
/1Layer1/OUT_P3: R113.2, R114.2, R115.2, R116.2, R117.2, R118.2, R119.2; also elsewhere on the board
/1Layer1/OUT_P4: R127.2, R128.2, R129.2, R130.2, R131.2, R132.2, R133.2; also elsewhere on the board
/1Layer1/OUT_P5: R141.2, R142.2, R143.2, R144.2, R145.2, R146.2, R147.2; also elsewhere on the board
/1Layer1/OUT_P6: R155.2, R156.2, R157.2, R158.2, R159.2, R160.2, R161.2; also elsewhere on the board
/1Layer1/VREF: R85.1, R92.1, R99.1, R106.1, R113.1, R120.1, R127.1, R134.1, R141.1, R148.1, R155.1, R162.1; also elsewhere on the board
/1Layer2/IN1: R170.1, R177.1, R184.1, R191.1, R198.1, R205.1, R212.1, R219.1, R226.1, R233.1, R240.1, R247.1; also elsewhere on the board
/1Layer2/IN2: R171.1, R178.1, R185.1, R192.1, R199.1, R206.1, R213.1, R220.1, R227.1, R234.1, R241.1, R248.1; also elsewhere on the board
/1Layer2/IN3: R172.1, R179.1, R186.1, R193.1, R200.1, R207.1, R214.1, R221.1, R228.1, R235.1, R242.1, R249.1; also elsewhere on the board
/1Layer2/IN4: R173.1, R180.1, R187.1, R194.1, R201.1, R208.1, R215.1, R222.1, R229.1, R236.1, R243.1, R250.1; also elsewhere on the board
/1Layer2/IN5: R174.1, R181.1, R188.1, R195.1, R202.1, R209.1, R216.1, R223.1, R230.1, R237.1, R244.1, R251.1; also elsewhere on the board
/1Layer2/IN6: R175.1, R182.1, R189.1, R196.1, R203.1, R210.1, R217.1, R224.1, R231.1, R238.1, R245.1, R252.1; also elsewhere on the board
/1Layer2/OUT_N1: R176.2, R177.2, R178.2, R179.2, R180.2, R181.2, R182.2; also elsewhere on the board
/1Layer2/OUT_N2: R190.2, R191.2, R192.2, R193.2, R194.2, R195.2, R196.2; also elsewhere on the board
/1Layer2/OUT_N3: R204.2, R205.2, R206.2, R207.2, R208.2, R209.2, R210.2; also elsewhere on the board
/1Layer2/OUT_N4: R218.2, R219.2, R220.2, R221.2, R222.2, R223.2, R224.2; also elsewhere on the board
/1Layer2/OUT_N5: R232.2, R233.2, R234.2, R235.2, R236.2, R237.2, R238.2; also elsewhere on the board
/1Layer2/OUT_N6: R246.2, R247.2, R248.2, R249.2, R250.2, R251.2, R252.2; also elsewhere on the board
/1Layer2/OUT_P1: R169.2, R170.2, R171.2, R172.2, R173.2, R174.2, R175.2; also elsewhere on the board
/1Layer2/OUT_P2: R183.2, R184.2, R185.2, R186.2, R187.2, R188.2, R189.2; also elsewhere on the board
/1Layer2/OUT_P3: R197.2, R198.2, R199.2, R200.2, R201.2, R202.2, R203.2; also elsewhere on the board
/1Layer2/OUT_P4: R211.2, R212.2, R213.2, R214.2, R215.2, R216.2, R217.2; also elsewhere on the board
/1Layer2/OUT_P5: R225.2, R226.2, R227.2, R228.2, R229.2, R230.2, R231.2; also elsewhere on the board
/1Layer2/OUT_P6: R239.2, R240.2, R241.2, R242.2, R243.2, R244.2, R245.2; also elsewhere on the board
/1Layer2/VREF: R169.1, R176.1, R183.1, R190.1, R197.1, R204.1, R211.1, R218.1, R225.1, R232.1, R239.1, R246.1; also elsewhere on the board
/1Layer/IN1: R16.1, R23.1, R30.1, R37.1, R44.1, R51.1, R58.1, R65.1, R72.1, R79.1; also elsewhere on the board
/1Layer/IN2: R17.1, R24.1, R31.1, R38.1, R45.1, R52.1, R59.1, R66.1, R73.1, R80.1; also elsewhere on the board
/1Layer/IN3: R18.1, R25.1, R32.1, R39.1, R46.1, R53.1, R60.1, R67.1, R74.1, R81.1; also elsewhere on the board
/1Layer/IN4: R19.1, R26.1, R33.1, R40.1, R47.1, R54.1, R61.1, R68.1, R75.1, R82.1; also elsewhere on the board
/1Layer/IN5: R20.1, R27.1, R34.1, R41.1, R48.1, R55.1, R62.1, R69.1, R76.1, R83.1; also elsewhere on the board
/1Layer/IN6: R21.1, R28.1, R35.1, R42.1, R49.1, R56.1, R63.1, R70.1, R77.1, R84.1; also elsewhere on the board
/1Layer/OUT_N2: R22.2, R23.2, R24.2, R25.2, R26.2, R27.2, R28.2; also elsewhere on the board
/1Layer/OUT_N3: R36.2, R37.2, R38.2, R39.2, R40.2, R41.2, R42.2; also elsewhere on the board
/1Layer/OUT_N4: R50.2, R51.2, R52.2, R53.2, R54.2, R55.2, R56.2; also elsewhere on the board
/1Layer/OUT_N5: R64.2, R65.2, R66.2, R67.2, R68.2, R69.2, R70.2; also elsewhere on the board
/1Layer/OUT_N6: R78.2, R79.2, R80.2, R81.2, R82.2, R83.2, R84.2; also elsewhere on the board
/1Layer/OUT_P2: R15.2, R16.2, R17.2, R18.2, R19.2, R20.2, R21.2; also elsewhere on the board
/1Layer/OUT_P3: R29.2, R30.2, R31.2, R32.2, R33.2, R34.2, R35.2; also elsewhere on the board
/1Layer/OUT_P4: R43.2, R44.2, R45.2, R46.2, R47.2, R48.2, R49.2; also elsewhere on the board
/1Layer/OUT_P5: R57.2, R58.2, R59.2, R60.2, R61.2, R62.2, R63.2; also elsewhere on the board
/1Layer/OUT_P6: R71.2, R72.2, R73.2, R74.2, R75.2, R76.2, R77.2; also elsewhere on the board
/1Layer/VREF: R15.1, R22.1, R29.1, R36.1, R43.1, R50.1, R57.1, R64.1, R71.1, R78.1; also elsewhere on the board
/OUTLAYER_IN1: R254.1, R261.1; also elsewhere on the board
/OUTLAYER_IN2: R255.1, R262.1; also elsewhere on the board
/OUTLAYER_IN3: R256.1, R263.1; also elsewhere on the board
/OUTLAYER_IN4: R257.1, R264.1; also elsewhere on the board
/OUTLAYER_IN5: R258.1, R265.1; also elsewhere on the board
/OUTLAYER_IN6: R259.1, R266.1; also elsewhere on the board
/OUTLAYER_OUT_N1: R260.2, R261.2, R262.2, R263.2, R264.2, R265.2, R266.2; also elsewhere on the board
/OUTLAYER_OUT_P1: R253.2, R254.2, R255.2, R256.2, R257.2, R258.2, R259.2; also elsewhere on the board
/VREF: R253.1, R260.1; also elsewhere on the board

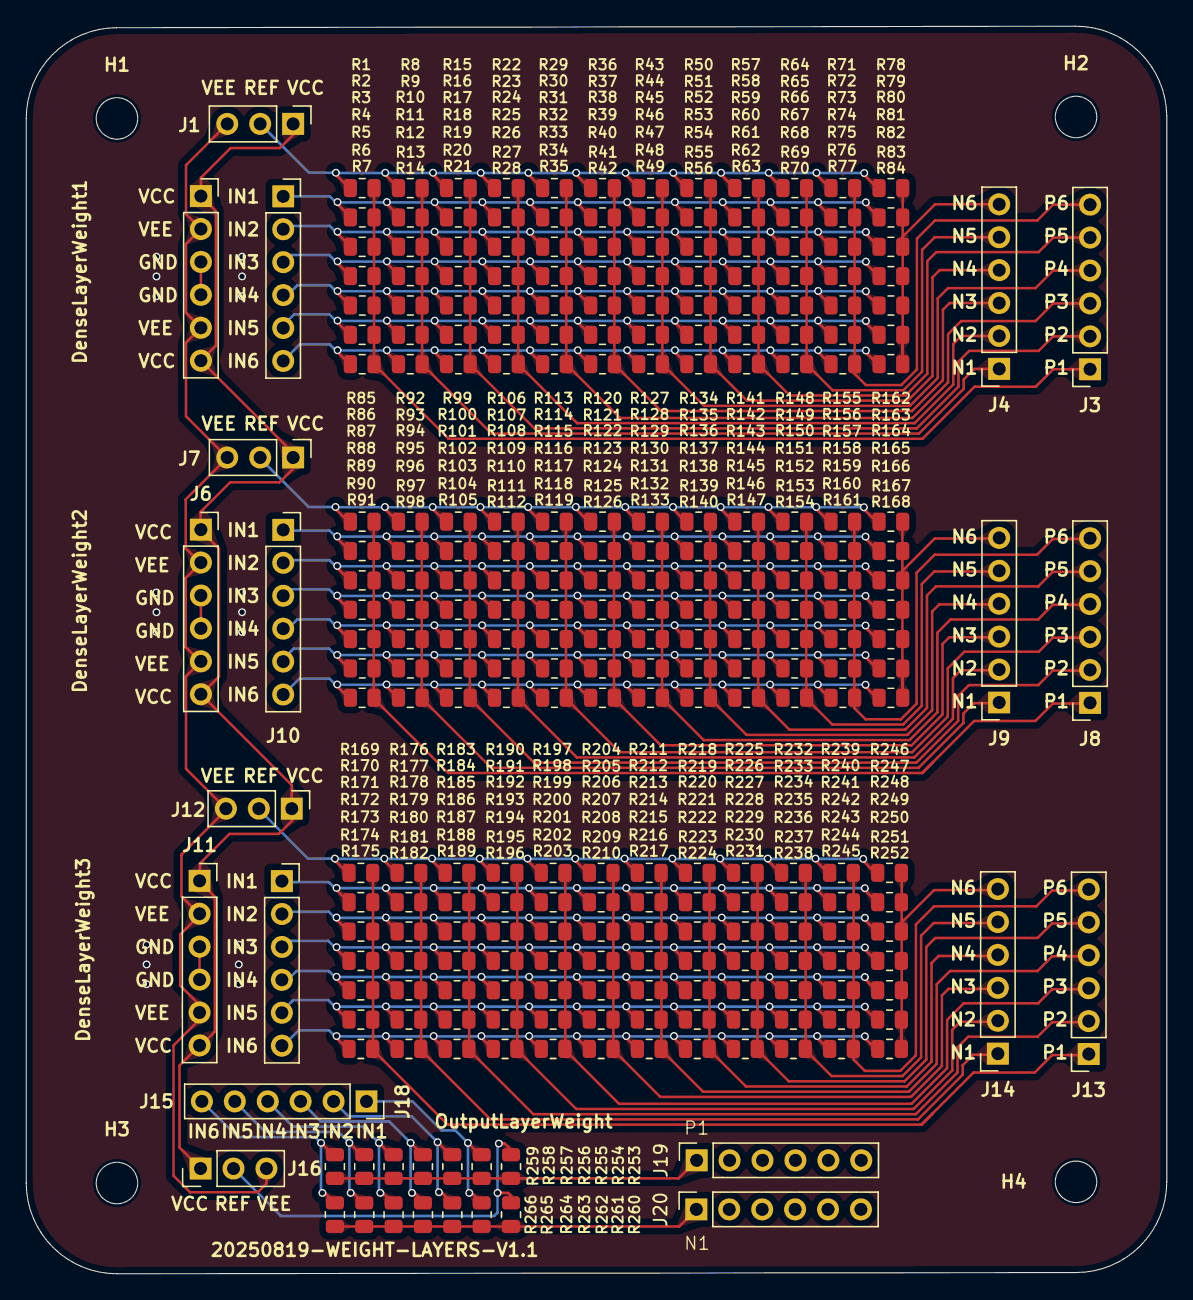
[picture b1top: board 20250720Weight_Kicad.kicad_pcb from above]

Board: 2 copper layers, 88.0 x 96.3 mm, 289 parts (0 on the bottom side), 69 nets.

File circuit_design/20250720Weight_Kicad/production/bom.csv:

Designator,Footprint,Quantity,Value,LCSC Part #
"J1, J12, J16, J7",PinHeader_1x03_P2.54mm_Vertical,4,Conn_01x03,
"J10, J11, J13, J14, J15, J18, J19, J2, J20, J3, J4, J5, J6, J8, J9",PinSocket_1x06_P2.54mm_Vertical,15,Conn_01x06,
"R1, R10, R100, R101, R102, R103, R104, R105, R106, R107, R108, R109, R11, R110, R111, R112, R113, R114, R115, R116, R117, R118, R119, R12, R120, R121, R122, R123, R124, R125, R126, R127, R128, R129, R13, R130, R131, R132, R133, R134, R135, R136, R137, R138, R139, R14, R140, R141, R142, R143, R144, R145, R146, R147, R148, R149, R15, R150, R151, R152, R153, R154, R155, R156, R157, R158, R159, R16, R160, R161, R162, R163, R164, R165, R166, R167, R168, R169, R17, R170, R171, R172, R173, R174, R175, R176, R177, R178, R179, R18, R180, R181, R182, R183, R184, R185, R186, R187, R188, R189, R19, R190, R191, R192, R193, R194, R195, R196, R197, R198, R199, R2, R20, R200, R201, R202, R203, R204, R205, R206, R207, R208, R209, R21, R210, R211, R212, R213, R214, R215, R216, R217, R218, R219, R22, R220, R221, R222, R223, R224, R225, R226, R227, R228, R229, R23, R230, R231, R232, R233, R234, R235, R236, R237, R238, R239, R24, R240, R241, R242, R243, R244, R245, R246, R247, R248, R249, R25, R250, R251, R252, R253, R254, R255, R256, R257, R258, R259, R26, R260, R261, R262, R263, R264, R265, R266, R27, R28, R29, R3, R30, R31, R32, R33, R34, R35, R36, R37, R38, R39",0805,200,1K,
"R4, R40, R41, R42, R43, R44, R45, R46, R47, R48, R49, R5, R50, R51, R52, R53, R54, R55, R56, R57, R58, R59, R6, R60, R61, R62, R63, R64, R65, R66, R67, R68, R69, R7, R70, R71, R72, R73, R74, R75, R76, R77, R78, R79, R8, R80, R81, R82, R83, R84, R85, R86, R87, R88, R89, R9, R90, R91, R92, R93, R94, R95, R96, R97, R98, R99",0805,66,1K,

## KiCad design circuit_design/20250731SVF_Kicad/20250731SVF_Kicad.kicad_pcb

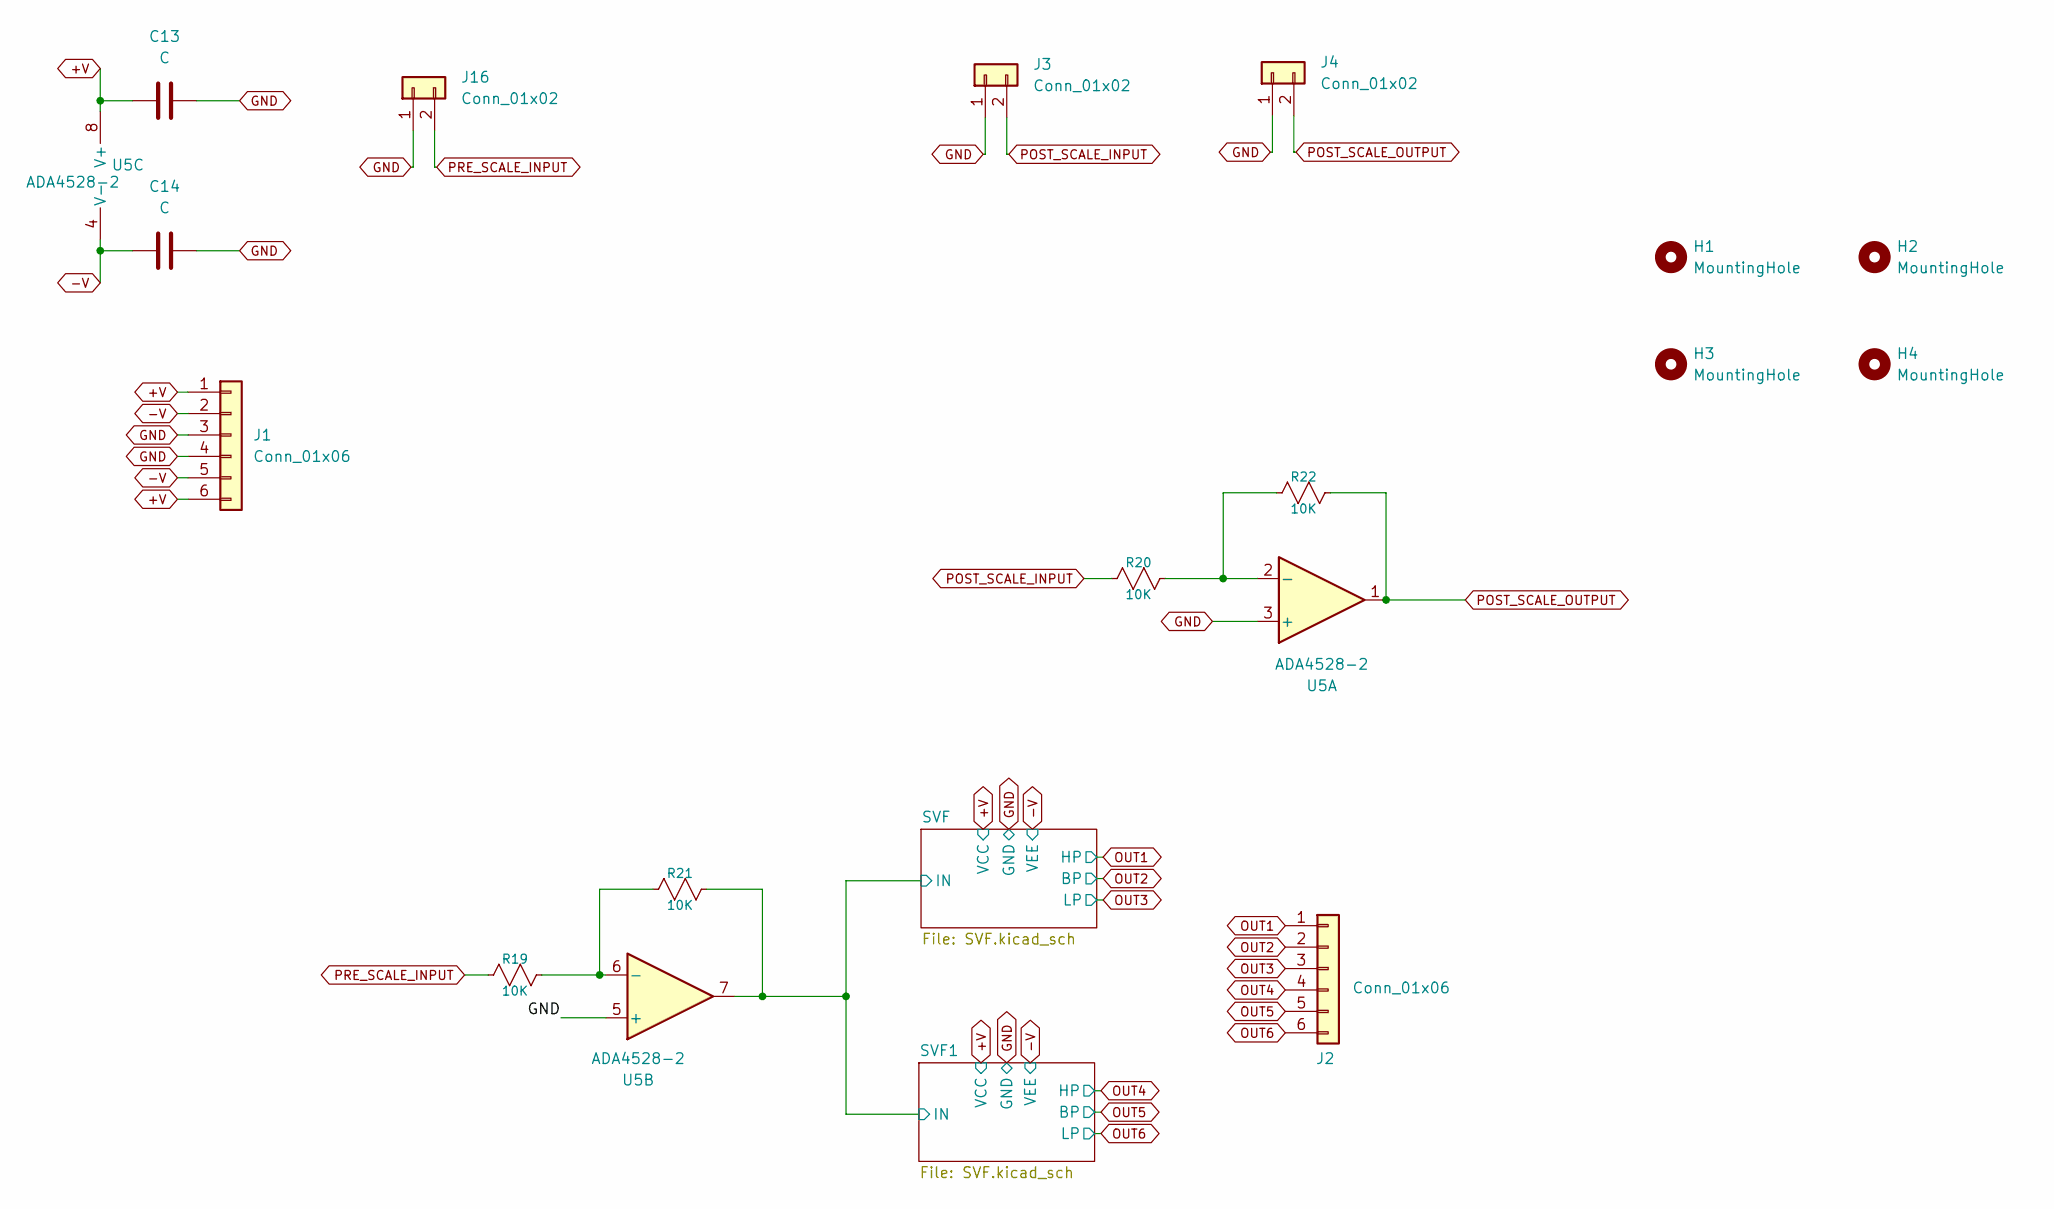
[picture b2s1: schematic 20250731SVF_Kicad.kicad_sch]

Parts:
C13, C14: C; C_0805_2012Metric
H1, H2, H3, H4: MountingHole; MountingHole_3.2mm_M3
J1, J2: Conn_01x06; PinSocket_1x06_P2.54mm_Vertical
J3, J4, J16: Conn_01x02; PinHeader_1x02_P2.54mm_Vertical
R19, R20, R21, R22: 10K; R_0805_2012Metric
U5: ADA4528-2; MSOP-8_3x3mm_P0.65mm

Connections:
+V: C13.1, J1.1, J1.6, U5.8 (V+); also elsewhere on the board
-V: C14.1, J1.2, J1.5, U5.4 (V-); also elsewhere on the board
/SVF/IN: R21.1, U5.7; also elsewhere on the board
GND: C13.2, C14.2, J1.3, J1.4, J3.1, J4.1, J16.1, U5.3 (+), U5.5 (+); also elsewhere on the board
unnamed: R20.1, R22.2, U5.2 (-)
unnamed: R19.1, R21.2, U5.6 (-)
OUT1: J2.1; also elsewhere on the board
OUT2: J2.2; also elsewhere on the board
OUT3: J2.3; also elsewhere on the board
OUT4: J2.4; also elsewhere on the board
OUT5: J2.5; also elsewhere on the board
OUT6: J2.6; also elsewhere on the board
POST_SCALE_INPUT: J3.2, R20.2
POST_SCALE_OUTPUT: J4.2, R22.1, U5.1
PRE_SCALE_INPUT: J16.2, R19.2
